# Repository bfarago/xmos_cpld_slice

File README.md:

# xmos_cpld_slice
This is a slice extender panel, which contains a small cpld, aimed to have configurable the bridge between the slot and the slice panel.

[The page of the project](https://bfarago.github.io/xmos_cpld_slice/)

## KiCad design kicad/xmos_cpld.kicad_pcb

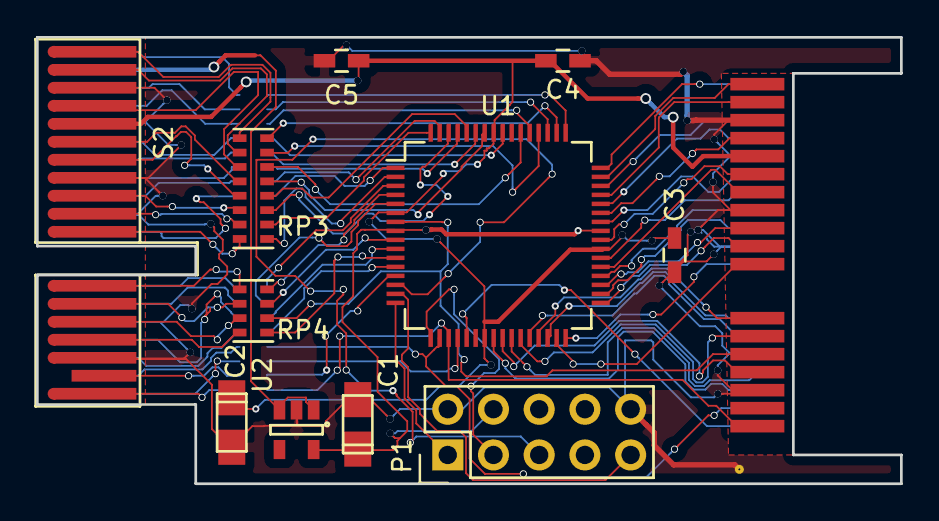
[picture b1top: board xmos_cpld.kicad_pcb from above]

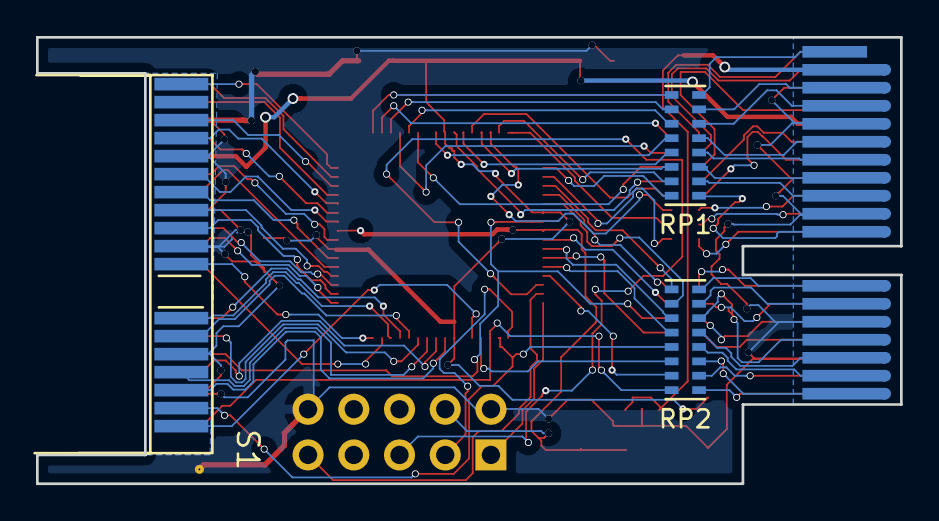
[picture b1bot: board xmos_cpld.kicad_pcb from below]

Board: 2 copper layers, 48.0 x 24.8 mm, 15 parts (3 on the bottom side), 90 nets.

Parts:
C1, C2: 2u2; TantalC_SizeS_EIA-3216
C3, C4, C5: 100N; C_0603_HandSoldering
P1: CONN_02X05; Pin_Header_Straight_2x05
P16: Pillar
RP1, RP2, RP3: 33R; R_Cat16-8
RP4: 33R; R_Cat16-4
S1: SlicePcbCon; PCIe_36
S2: SlicePcbCon; PCI-EXPRESS
U1: 5M40ZE64; LQFP-64_10x10mm_Pitch0.5mm
U2: NCP699SN18; SOT-23-5

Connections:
+1V8: C1.1, P1.4, U1.8, U1.41, U2.5
+3V3: C2.1, C3.1, C4.1, C5.1, S1.B5, S2.B5, U1.6, U1.23, U1.39, U1.57
+5V: S1.A2, S2.A2, U2.1, U2.3
/AA1: RP1.1, U1.49
/AA3: RP1.2, U1.51
/AA4: RP1.3, U1.53
/AA6: RP1.4, U1.56
/AA7: RP1.5, U1.59
/AA8: RP1.6, U1.61
/AA9: RP1.7, U1.63
/AA11: RP1.8, U1.1
/AA12: RP2.1, U1.3
/AA13: RP2.2, U1.5
/AA15: RP2.3, U1.10
/AA16: RP2.4, U1.12
/AA18: RP2.6, U1.55
/AB1: RP3.16, U1.50
/AB2: RP3.15, U1.52
/AB4: RP3.14, U1.54
/AB6: RP3.13, U1.58
/AB7: RP3.12, U1.60
/AB9: RP3.11, U1.62
/AB10: RP3.10, U1.64
/AB11: RP3.9, U1.2
/AB12: RP4.8, U1.4
/AB13: RP4.7, U1.9
/AB15: RP4.5, U1.11
/AB17: RP2.7, U1.13
/AB18: RP2.8, U1.19
/ACLK: RP4.6, S1.B14, U1.7
/BA1: S1.A1, U1.48
/BA3: S1.A3, U1.46
/BA4: S1.A4, U1.44
/BA6: S1.A6, U1.42
/BA7: S1.A7, U1.38
/BA8: S1.A8, U1.36
/BA9: S1.A9, U1.34
/BA11: S1.A11, U1.32
/BA12: S1.A12, U1.30
/BA13: S1.A13, U1.28
/BA15: S1.A15, U1.26
/BA16: S1.A16, U1.24
/BA18: S1.A18, U1.21
/BB1: S1.B1, U1.47
/BB2: S1.B2, U1.45
/BB4: S1.B4, U1.43
/BB6: S1.B6, U1.40
/BB7: S1.B7, U1.37
/BB9: S1.B9, U1.35
/BB10: S1.B10, U1.33
/BB11: S1.B11, U1.31
/BB12: S1.B12, U1.29
/BB13: S1.B13, U1.27
/BB15: S1.B15, U1.25
/BB17: S1.B17, U1.22
/BB18: S1.B18, U1.20
/F1TCK: P1.1, U1.16
/F1TDI: P1.9, U1.15
/F1TDO: P1.3, U1.17
/F1TMS: P1.5, U1.14
/~ARST: RP2.5, S1.A17, U1.18
GND: C1.2, C2.2, C3.2, C4.2, C5.2, P1.2, P1.10, P16.1, S1.A5, S1.A10, S1.A14, S1.B3, S1.B8, S1.B16, S2.A5, S2.A10, S2.A14, S2.B3, S2.B8, S2.B16, U2.2
unnamed: RP1.9, S2.A11
unnamed: RP1.10, S2.A9
unnamed: RP1.11, S2.A8
unnamed: RP1.12, S2.A7
unnamed: RP1.13, S2.A6
unnamed: RP1.14, S2.A4
unnamed: RP1.15, S2.A3
unnamed: RP1.16, S2.A1
unnamed: RP2.9, S2.B18
unnamed: RP2.10, S2.B17
unnamed: RP2.11, S2.A18
unnamed: RP2.12, S2.A17
unnamed: RP2.13, S2.A16
unnamed: RP2.14, S2.A15
unnamed: RP2.15, S2.A13
unnamed: RP2.16, S2.A12
unnamed: RP3.1, S2.B1
unnamed: RP3.2, S2.B2
unnamed: RP3.3, S2.B4
unnamed: RP3.4, S2.B6
unnamed: RP3.5, S2.B7
unnamed: RP3.6, S2.B9
unnamed: RP3.7, S2.B10
unnamed: RP3.8, S2.B11
unnamed: RP4.1, S2.B12
unnamed: RP4.2, S2.B13
unnamed: RP4.3, S2.B14
unnamed: RP4.4, S2.B15

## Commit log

2016-09-11 Create gh-pages branch via GitHub
2016-09-11 doc added
2016-09-11 kicad project added
2016-09-11 first cpld design
2016-09-11 ultimate++ desktop app added
2016-09-11 some images added
2016-09-11 Something...
2016-09-11 more img added
2016-09-11 typo
2016-09-11 verilog gen, screensh.
2016-09-12 1V8 pwr chip goes to other edge of the board. GND zones added.
2016-09-12 add p55, gnd.
2016-09-14 add xpin verilog, qsf export. More pin descriptions.
2016-09-15 Add ports
2016-09-15 GPIO board added
2016-09-16 several boards added
